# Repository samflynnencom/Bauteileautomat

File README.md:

Bauteileautomat
===============

This project merges the three branches of the student project "Bauteileautomat", a component vending machine built by students of the university of applied sciences Karlsruhe.
We all know the problem of working on a specific project and suddenly you encounter a missing part. And often it is a pretty common part like a 47k resistor you forgot to restock. That's where our vending machine comes into play. the machine holds the most common components and offers them to the students on the cheap.

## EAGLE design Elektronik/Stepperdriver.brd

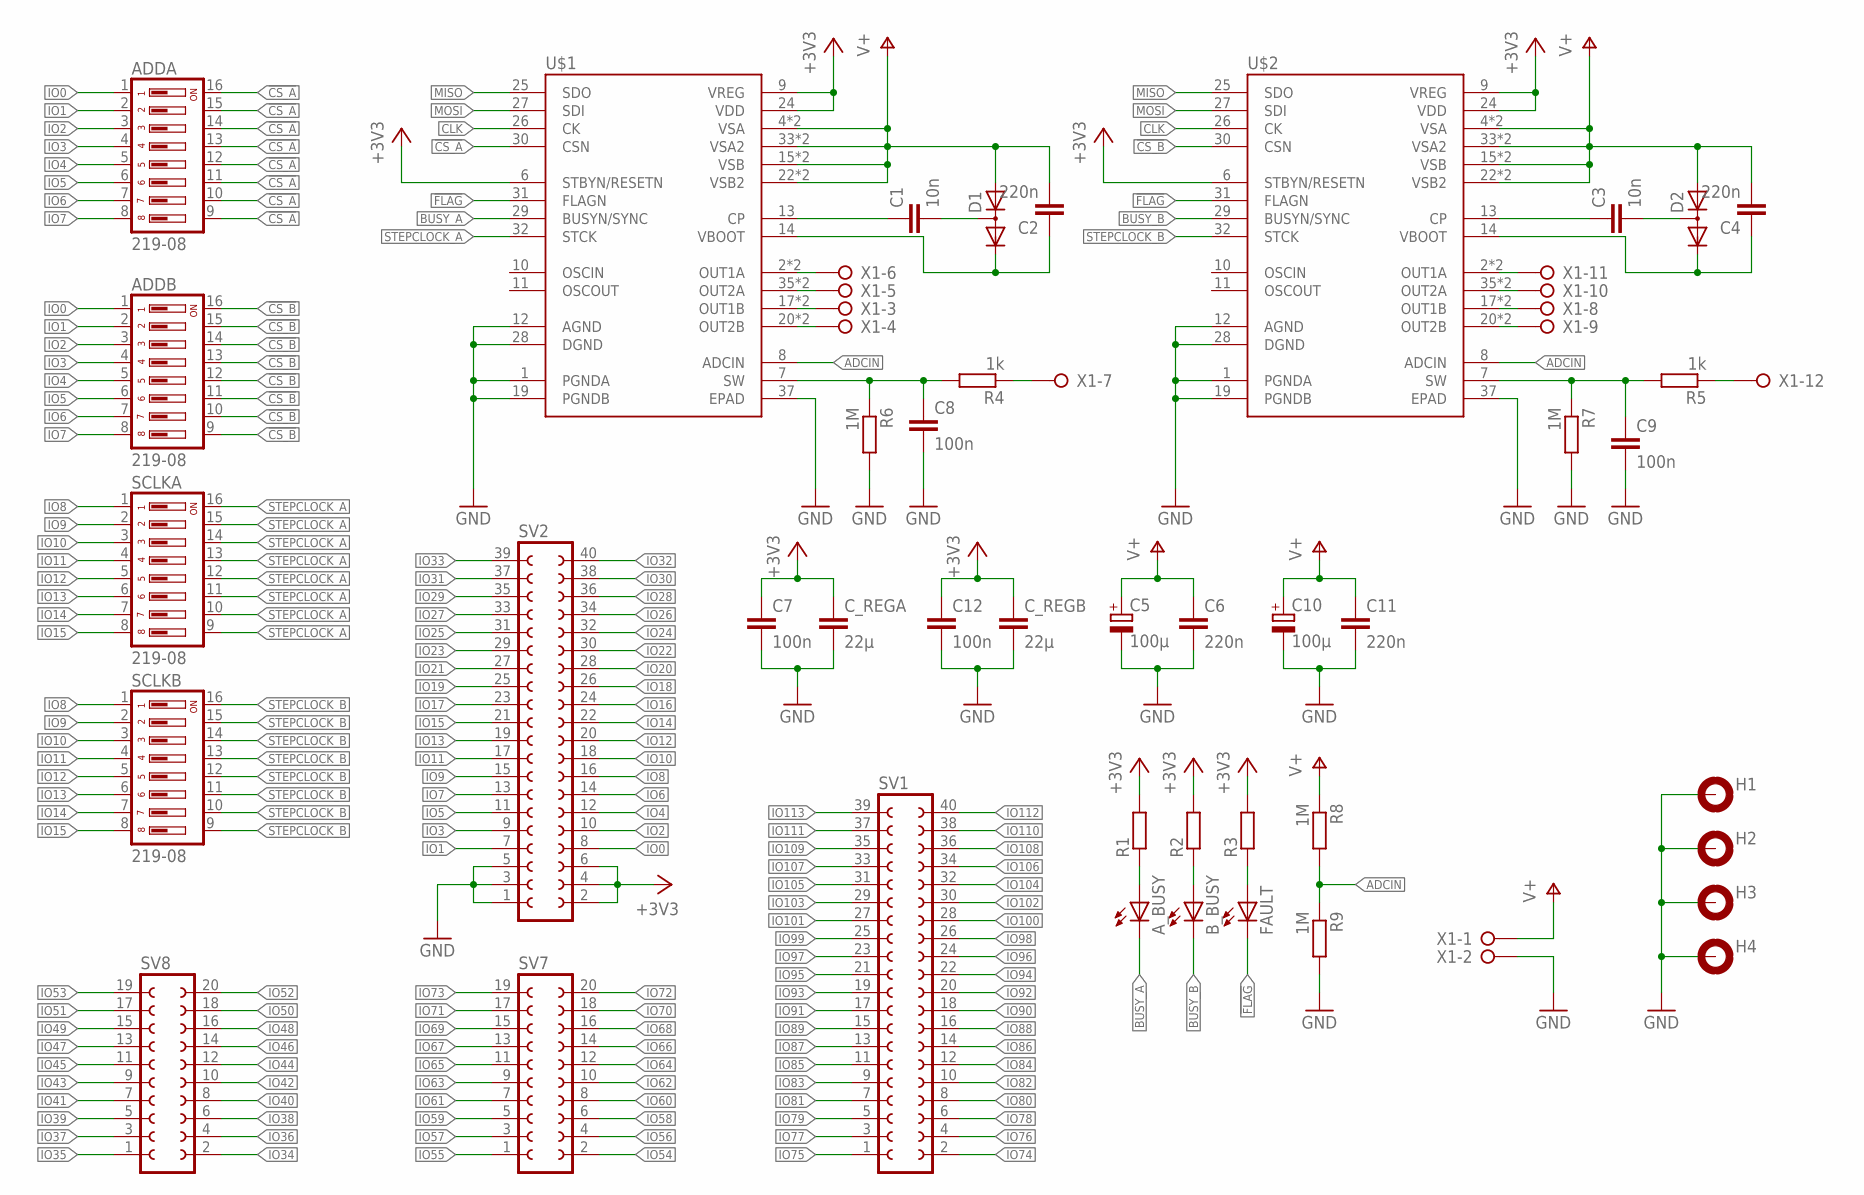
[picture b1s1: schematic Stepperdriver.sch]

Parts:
ADDA: 219-08; CTS-219-08
ADDB: 219-08; CTS-219-08
A_BUSY: LEDCHIP-LED0805; CHIP-LED0805
B_BUSY: LEDCHIP-LED0805; CHIP-LED0805
C1, C3: 10n; C0805
C2, C4, C6, C11: 220n; C0805
C5, C10: 100µ; 150CLZ-1010
C7, C8, C9, C12: 100n; C0805
C_REGA: 22µ; C0805
C_REGB: 22µ; C0805
D1, D2: DIODE_2CACA-SOT23; SOT23
FAULT: LEDCHIP-LED0805; CHIP-LED0805
H1, H2, H3, H4: MOUNT-PAD-ROUND5.0; 5,0-PAD
R1, R2, R3: R-EU_R0805; R0805
R4, R5: 1k; R0805
R6, R7, R8, R9: 1M; R0805
SCLKA: 219-08; CTS-219-08
SCLKB: 219-08; CTS-219-08
SV1, SV2: FE20-2
SV7, SV8: FE10-2
U$1, U$2: L6470HPOWERSO36; SOP65P1400X360-37N
X1: W237-12P

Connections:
!CS_A: ADDA.9, ADDA.10, ADDA.11, ADDA.12, ADDA.13, ADDA.14, ADDA.15, ADDA.16, U$1.30 (CSN)
!CS_B: ADDB.9, ADDB.10, ADDB.11, ADDB.12, ADDB.13, ADDB.14, ADDB.15, ADDB.16, U$2.30 (CSN)
!FLAG: FAULT.C, U$1.31 (FLAGN), U$2.31 (FLAGN)
+3V3: C7.1, C12.1, C_REGA.1, C_REGB.1, R1.2, R2.2, R3.2, SV2.2, SV2.4, SV2.6, U$1.6 (STBYN/RESETN), U$1.9 (VREG), U$1.24 (VDD), U$2.6 (STBYN/RESETN), U$2.9 (VREG), U$2.24 (VDD)
ADCIN: R8.2, R9.1, U$1.8 (ADCIN), U$2.8 (ADCIN)
BUSY_A: A_BUSY.C, U$1.29 (BUSYN/SYNC)
BUSY_B: B_BUSY.C, U$2.29 (BUSYN/SYNC)
CLK: U$1.26 (CK), U$2.26 (CK)
GND: C5.-, C6.2, C7.2, C8.2, C9.2, C10.-, C11.2, C12.2, C_REGA.2, C_REGB.2, H1.B5, H2.B5, H3.B5, H4.B5, R6.2, R7.2, R9.2, SV2.1, SV2.3, SV2.5, U$1.1 (PGNDA), U$1.12 (AGND), U$1.19 (PGNDB), U$1.28 (DGND), U$1.37 (EPAD), U$2.1 (PGNDA), U$2.12 (AGND), U$2.19 (PGNDB), U$2.28 (DGND), U$2.37 (EPAD), X1.2
IO0: ADDA.1, ADDB.1, SV2.8
IO1: ADDA.2, ADDB.2, SV2.7
IO2: ADDA.3, ADDB.3, SV2.10
IO3: ADDA.4, ADDB.4, SV2.9
IO4: ADDA.5, ADDB.5, SV2.12
IO5: ADDA.6, ADDB.6, SV2.11
IO6: ADDA.7, ADDB.7, SV2.14
IO7: ADDA.8, ADDB.8, SV2.13
IO8: SCLKA.1, SCLKB.1, SV2.16
IO9: SCLKA.2, SCLKB.2, SV2.15
IO10: SCLKA.3, SCLKB.3, SV2.18
IO11: SCLKA.4, SCLKB.4, SV2.17
IO12: SCLKA.5, SCLKB.5, SV2.20
IO13: SCLKA.6, SCLKB.6, SV2.19
IO14: SCLKA.7, SCLKB.7, SV2.22
IO15: SCLKA.8, SCLKB.8, SV2.21
IO16: SV2.24
IO17: SV2.23
IO18: SV2.26
IO19: SV2.25
IO20: SV2.28
IO21: SV2.27
IO22: SV2.30
IO23: SV2.29
IO24: SV2.32
IO25: SV2.31
IO26: SV2.34
IO27: SV2.33
IO28: SV2.36
IO29: SV2.35
IO30: SV2.38
IO31: SV2.37
IO32: SV2.40
IO33: SV2.39
IO34: SV8.2
IO35: SV8.1
IO36: SV8.4
IO37: SV8.3
IO38: SV8.6
IO39: SV8.5
IO40: SV8.8
IO41: SV8.7
IO42: SV8.10
IO43: SV8.9
IO44: SV8.12
IO45: SV8.11
IO46: SV8.14
IO47: SV8.13
IO48: SV8.16
IO49: SV8.15
IO50: SV8.18
IO51: SV8.17
IO52: SV8.20
IO53: SV8.19
IO54: SV7.2
IO55: SV7.1
IO56: SV7.4
IO57: SV7.3
IO58: SV7.6
IO59: SV7.5
IO60: SV7.8
IO61: SV7.7
IO62: SV7.10
IO63: SV7.9
IO64: SV7.12
IO65: SV7.11
IO66: SV7.14
IO67: SV7.13
IO68: SV7.16
IO69: SV7.15
IO70: SV7.18
IO71: SV7.17
IO72: SV7.20
IO73: SV7.19
IO74: SV1.2
IO75: SV1.1
IO76: SV1.4
IO77: SV1.3
IO78: SV1.6
IO79: SV1.5
IO80: SV1.8
IO81: SV1.7
IO82: SV1.10
IO83: SV1.9
IO84: SV1.12
IO85: SV1.11
IO86: SV1.14
IO87: SV1.13
IO88: SV1.16
IO89: SV1.15
IO90: SV1.18
IO91: SV1.17
IO92: SV1.20
IO93: SV1.19
IO94: SV1.22
IO95: SV1.21
IO96: SV1.24
IO97: SV1.23
IO98: SV1.26
IO99: SV1.25
IO100: SV1.28
IO101: SV1.27
IO102: SV1.30
IO103: SV1.29
IO104: SV1.32
IO105: SV1.31
IO106: SV1.34
IO107: SV1.33
IO108: SV1.36
IO109: SV1.35
IO110: SV1.38
IO111: SV1.37
IO112: SV1.40
IO113: SV1.39
MISO: U$1.25 (SDO), U$2.25 (SDO)
MOSI: U$1.27 (SDI), U$2.27 (SDI)
unnamed: U$1.2 (OUT1A), U$1.3 (OUT1A), X1.6
unnamed: U$1.35 (OUT2A), U$1.36 (OUT2A), X1.5
unnamed: U$1.17 (OUT1B), U$1.18 (OUT1B), X1.3
unnamed: U$1.20 (OUT2B), U$1.21 (OUT2B), X1.4
unnamed: U$2.20 (OUT2B), U$2.21 (OUT2B), X1.9
unnamed: U$2.17 (OUT1B), U$2.18 (OUT1B), X1.8
unnamed: U$2.35 (OUT2A), U$2.36 (OUT2A), X1.10
unnamed: U$2.2 (OUT1A), U$2.3 (OUT1A), X1.11
unnamed: C3.1, U$2.13 (CP)
unnamed: C3.2, D2.3 (AC)
unnamed: C4.1, D2.2 (C), U$2.14 (VBOOT)
unnamed: A_BUSY.A, R1.1
unnamed: C1.1, U$1.13 (CP)
unnamed: C1.2, D1.3 (AC)
unnamed: C2.1, D1.2 (C), U$1.14 (VBOOT)
unnamed: R5.1, X1.12
unnamed: B_BUSY.A, R2.1
unnamed: FAULT.A, R3.1
unnamed: C9.1, R5.2, R7.1, U$2.7 (SW)
unnamed: C8.1, R4.2, R6.1, U$1.7 (SW)
unnamed: R4.1, X1.7
STEPCLOCK_A: SCLKA.9, SCLKA.10, SCLKA.11, SCLKA.12, SCLKA.13, SCLKA.14, SCLKA.15, SCLKA.16, U$1.32 (STCK)
STEPCLOCK_B: SCLKB.9, SCLKB.10, SCLKB.11, SCLKB.12, SCLKB.13, SCLKB.14, SCLKB.15, SCLKB.16, U$2.32 (STCK)
V+: C2.2, C4.2, C5.+, C6.1, C10.+, C11.1, D1.1 (A), D2.1 (A), R8.1, U$1.4 (VSA), U$1.5 (VSA), U$1.15 (VSB), U$1.16 (VSB), U$1.22 (VSB2), U$1.23 (VSB2), U$1.33 (VSA2), U$1.34 (VSA2), U$2.4 (VSA), U$2.5 (VSA), U$2.15 (VSB), U$2.16 (VSB), U$2.22 (VSB2), U$2.23 (VSB2), U$2.33 (VSA2), U$2.34 (VSA2), X1.1

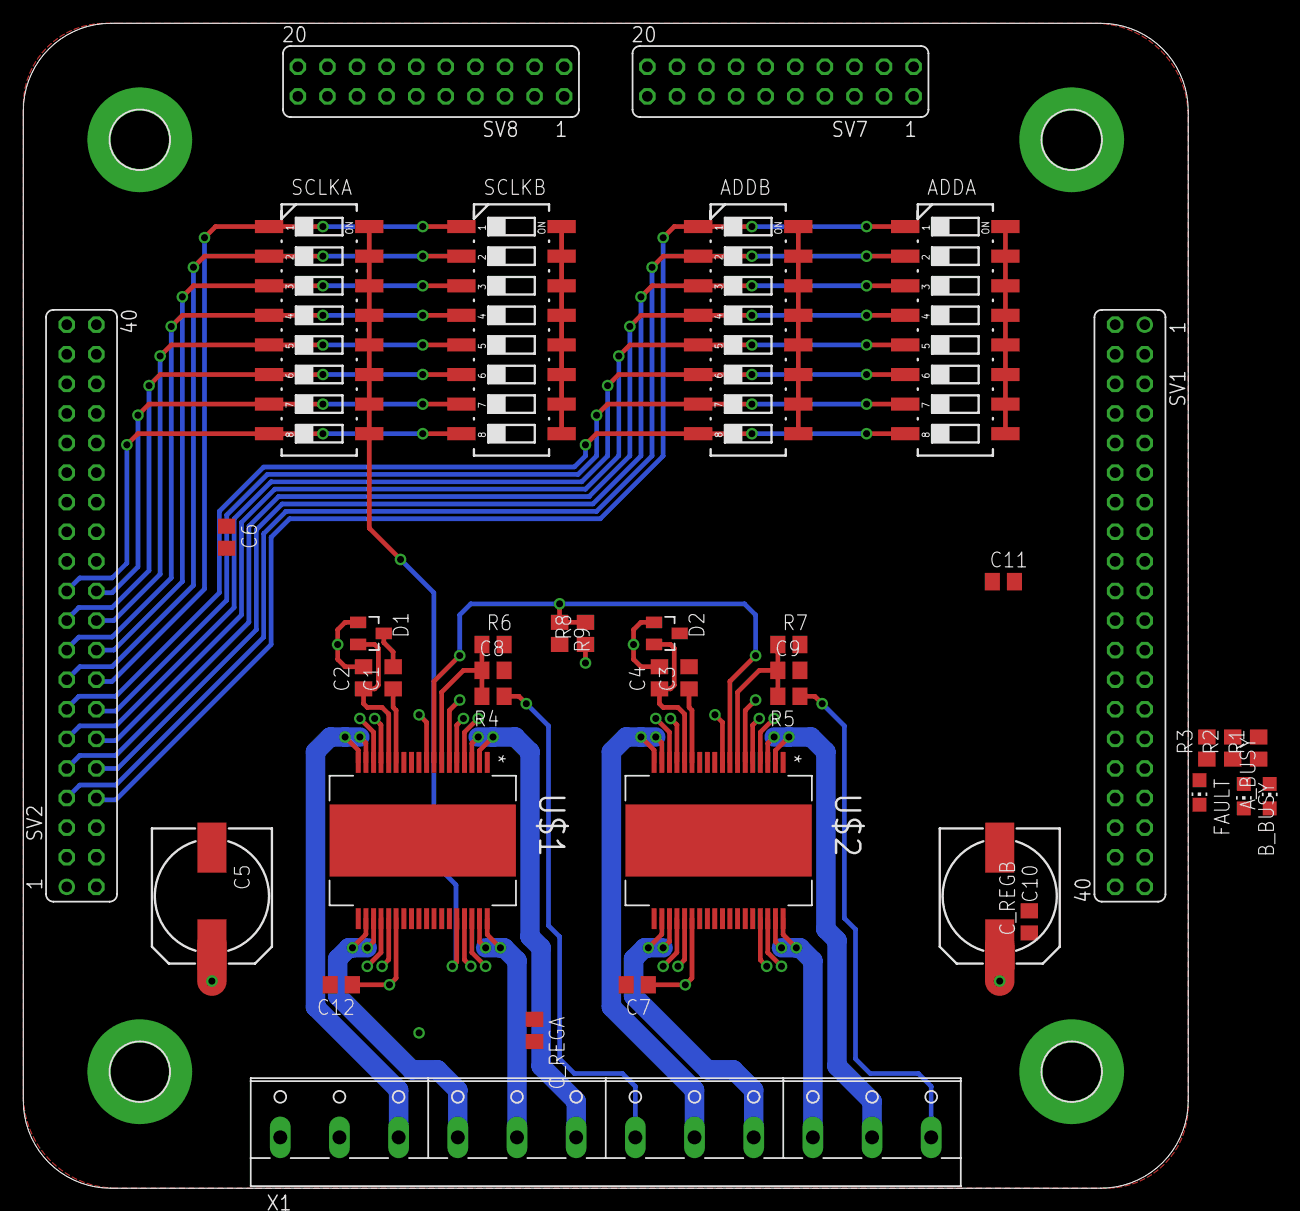
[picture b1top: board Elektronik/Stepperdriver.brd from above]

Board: 4 copper layers, 100.0 x 100.0 mm, 43 parts (0 on the bottom side), 51 nets.

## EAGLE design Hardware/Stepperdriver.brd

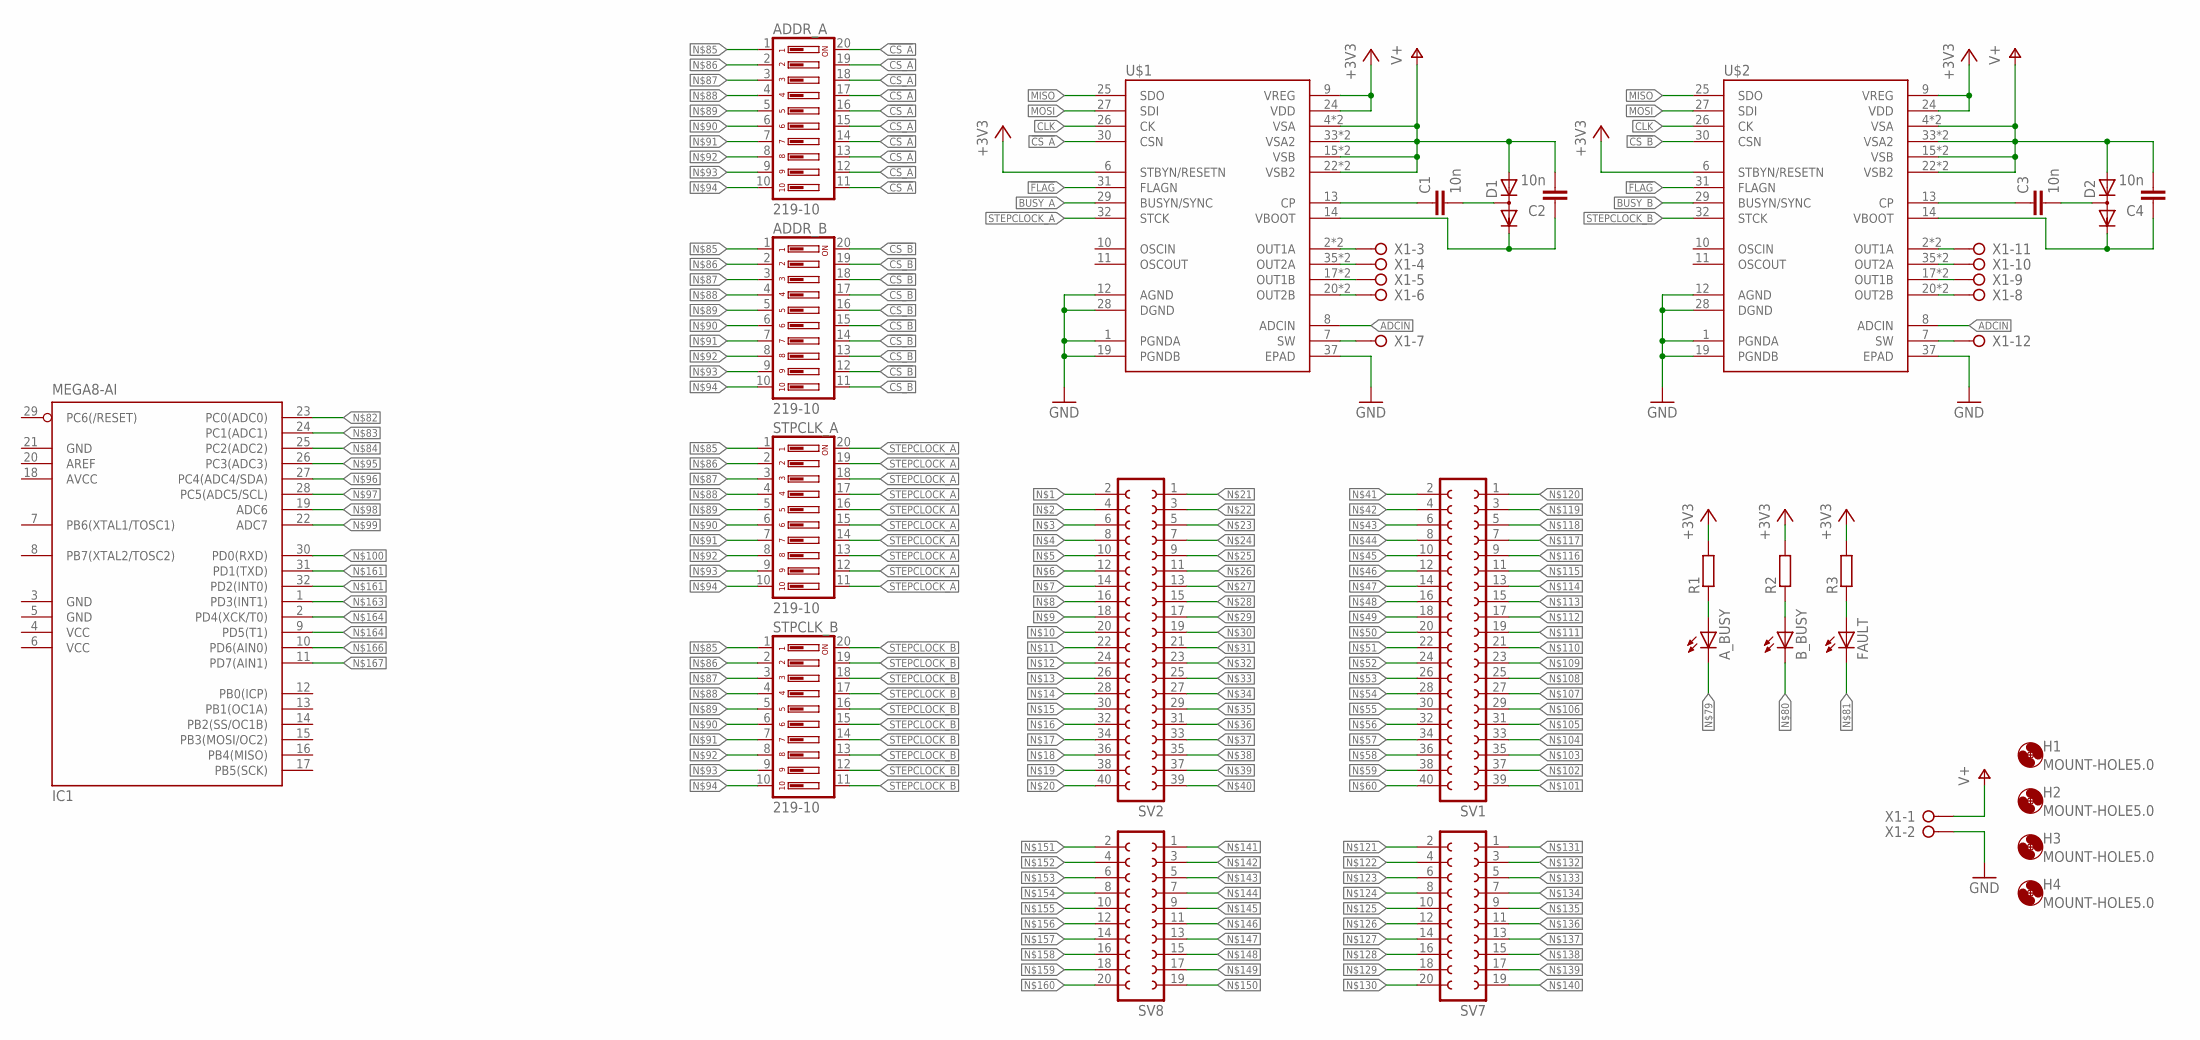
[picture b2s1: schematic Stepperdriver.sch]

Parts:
ADDR_A: 219-10; CTS-219-10
ADDR_B: 219-10; CTS-219-10
A_BUSY: LEDCHIP-LED0805; CHIP-LED0805
B_BUSY: LEDCHIP-LED0805; CHIP-LED0805
C1, C2, C3, C4: 10n; C0805
D1, D2: DIODE_2CACA-SOT23; SOT23
FAULT: LEDCHIP-LED0805; CHIP-LED0805
H1, H2, H3, H4: MOUNT-HOLE5.0; 5,0
IC1: MEGA8-AI; TQFP32-08
R1, R2, R3: R-EU_R0805; R0805
STPCLK_A: 219-10; CTS-219-10
STPCLK_B: 219-10; CTS-219-10
SV1, SV2: FE20-2
SV7, SV8: FE10-2
U$1, U$2: L6470HPOWERSO36; SOP65P1400X360-37N
X1: W237-12P

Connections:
!CS_A: ADDR_A.11, ADDR_A.12, ADDR_A.13, ADDR_A.14, ADDR_A.15, ADDR_A.16, ADDR_A.17, ADDR_A.18, ADDR_A.19, ADDR_A.20, U$1.30 (CSN)
!CS_B: ADDR_B.11, ADDR_B.12, ADDR_B.13, ADDR_B.14, ADDR_B.15, ADDR_B.16, ADDR_B.17, ADDR_B.18, ADDR_B.19, ADDR_B.20, U$2.30 (CSN)
!FLAG: U$1.31 (FLAGN), U$2.31 (FLAGN)
+3V3: R1.2, R2.2, R3.2, U$1.6 (STBYN/RESETN), U$1.9 (VREG), U$1.24 (VDD), U$2.6 (STBYN/RESETN), U$2.9 (VREG), U$2.24 (VDD)
ADCIN: U$1.8 (ADCIN), U$2.8 (ADCIN)
AVCC: IC1.18 (AVCC)
BUSY_A: U$1.29 (BUSYN/SYNC)
BUSY_B: U$2.29 (BUSYN/SYNC)
CLK: U$1.26 (CK), U$2.26 (CK)
GND: IC1.3 (GND), IC1.5 (GND), IC1.21 (GND), U$1.1 (PGNDA), U$1.12 (AGND), U$1.19 (PGNDB), U$1.28 (DGND), U$1.37 (EPAD), U$2.1 (PGNDA), U$2.12 (AGND), U$2.19 (PGNDB), U$2.28 (DGND), U$2.37 (EPAD), X1.2
MISO: U$1.25 (SDO), U$2.25 (SDO)
MOSI: U$1.27 (SDI), U$2.27 (SDI)
unnamed: C3.1, U$2.13 (CP)
unnamed: C3.2, D2.3 (AC)
unnamed: C4.1, D2.2 (C), U$2.14 (VBOOT)
unnamed: U$2.20 (OUT2B), U$2.21 (OUT2B), X1.8
unnamed: U$2.17 (OUT1B), U$2.18 (OUT1B), X1.9
unnamed: U$2.35 (OUT2A), U$2.36 (OUT2A), X1.10
unnamed: A_BUSY.A, R1.1
unnamed: U$2.2 (OUT1A), U$2.3 (OUT1A), X1.11
unnamed: U$1.2 (OUT1A), U$1.3 (OUT1A), X1.3
unnamed: U$1.35 (OUT2A), U$1.36 (OUT2A), X1.4
unnamed: C1.1, U$1.13 (CP)
unnamed: U$1.17 (OUT1B), U$1.18 (OUT1B), X1.5
unnamed: U$1.20 (OUT2B), U$1.21 (OUT2B), X1.6
unnamed: C1.2, D1.3 (AC)
unnamed: C2.1, D1.2 (C), U$1.14 (VBOOT)
unnamed: U$2.7 (SW), X1.12
unnamed: B_BUSY.A, R2.1
unnamed: FAULT.A, R3.1
unnamed: ADDR_A.1, ADDR_B.1, STPCLK_A.1, STPCLK_B.1
unnamed: ADDR_A.2, ADDR_B.2, STPCLK_A.2, STPCLK_B.2
unnamed: ADDR_A.3, ADDR_B.3, STPCLK_A.3, STPCLK_B.3
unnamed: ADDR_A.4, ADDR_B.4, STPCLK_A.4, STPCLK_B.4
unnamed: ADDR_A.5, ADDR_B.5, STPCLK_A.5, STPCLK_B.5
unnamed: ADDR_A.6, ADDR_B.6, STPCLK_A.6, STPCLK_B.6
unnamed: ADDR_A.7, ADDR_B.7, STPCLK_A.7, STPCLK_B.7
unnamed: ADDR_A.8, ADDR_B.8, STPCLK_A.8, STPCLK_B.8
unnamed: ADDR_A.9, ADDR_B.9, STPCLK_A.9, STPCLK_B.9
unnamed: ADDR_A.10, ADDR_B.10, STPCLK_A.10, STPCLK_B.10
STEPCLOCK_A: STPCLK_A.11, STPCLK_A.12, STPCLK_A.13, STPCLK_A.14, STPCLK_A.15, STPCLK_A.16, STPCLK_A.17, STPCLK_A.18, STPCLK_A.19, STPCLK_A.20, U$1.32 (STCK)
STEPCLOCK_B: STPCLK_B.11, STPCLK_B.12, STPCLK_B.13, STPCLK_B.14, STPCLK_B.15, STPCLK_B.16, STPCLK_B.17, STPCLK_B.18, STPCLK_B.19, STPCLK_B.20, U$2.32 (STCK)
SW_A: U$1.7 (SW), X1.7
V+: C2.2, C4.2, D1.1 (A), D2.1 (A), U$1.4 (VSA), U$1.5 (VSA), U$1.15 (VSB), U$1.16 (VSB), U$1.22 (VSB2), U$1.23 (VSB2), U$1.33 (VSA2), U$1.34 (VSA2), U$2.4 (VSA), U$2.5 (VSA), U$2.15 (VSB), U$2.16 (VSB), U$2.22 (VSB2), U$2.23 (VSB2), U$2.33 (VSA2), U$2.34 (VSA2), X1.1
VCC: IC1.4 (VCC), IC1.6 (VCC)

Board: 2 copper layers, 28 parts (0 on the bottom side), 42 nets, no tracks yet.

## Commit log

2014-06-01 Push um alles auf das Remote Repo zu bringen. Sortierung erfolgt hoffentlich im nächsten Commit.
2014-06-01 git fuckup
2014-06-29 Version 2 der Elektronik hinzugefügt. Modularisiert. WIP!
2014-07-13 test proxy
2014-07-13 Start der Umstellung auf das RTOS
2014-07-22 Elektronik auf den neusten Stand gebracht (Merge mit privater Dropbox
2014-07-22 Stepperendstufe weitergeroutet
2014-10-14 test commit
